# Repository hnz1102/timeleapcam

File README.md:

<div align="center">
  <h1><code>Time Leap Cam</code></h1>
  
</div>

# Time Leap Cam - Super Long Term Time-Lapse Camera and Monitoring by OpenAI

## Overview
The TIME LEAP CAM is an autofocus camera designed for long-duration time-lapse photography. Named for its ability to "leap" through time, this camera is ideal for monitoring over extended periods. It operates on battery power and features a DeepSleep mode to conserve energy when not actively shooting. Images are stored on a 64GB eMMC within one of eleven designated folders.

## What's New!
- 2024-08-12, If you want use on the XIAO ESP32S3 Sense module, please refer to the [XIAO_ESP32S3_SENSE branch](https://github.com/hnz1102/timeleapcam/tree/XIAO_ESP32S3_SENSE).

Update v0.3.3
- Improved the eMMC writing speed. The eMMC writing speed is improved by background writing. In the HD resolution, the writing speed is improved 28fps to 30fps. In the Full HD resolution, the writing speed is improved 6fps to 8fps. 
- JPEG quality can be set from 4 to 40. The default is 12. This value is high quality to set the value to 4. In the HD resolution, JPEG quality is set to less than 12, the writing speed is slower than 30fps. If you want to capture the image at 30fps, set the JPEG quality to 12 or more.
- If you want to direct write the image to the eMMC, set the 'Direct Write Mode' to checked. The image is directly written to the eMMC without the frame buffer. The writing speed is decreased. The default is unchecked.
- Changed the Allocate Unit Size to 32KB for the eMMC writing speed at the v0.3.3.

Update v0.3.2
- Add the 'System Temperature' to the status report. The temperature is measured by the internal temperature sensor of ESP32S3.
- Fixed the bug that when one-shot capture, the preview image is not displayed on the web.

Update v0.3.1
- Added the movie shooting function. The movie is created by combining the images taken at the specified cycle. 
 Capture Frames At Once (sec): The number of frames to capture at once. The default is 0, which means that the image is captured one by one. If you set it to 1, the image is captured during the 1 sec. If you set image resolution to VGA, the image is captured by 27 fps. HD is 15 - 27 fps. Full HD is 6 fps.
- Capture images are stored by appending the file. If you set to "Over Write Save", the image is overwritten. 
- Added the Open AI model 'GPT-4o mini' selection. The default is 'GPT-4o'. You can select the model from GPT-4o, GPT-4 Turbo, GPT-4o mini.
- If touch the button during 3 secs on the back, the camera starts the movie shooting. The movie shooting is stopped when the button is touched again.
- Improved the writing speed of the eMMC.
- Change the Report Interval: The default is 3600 sec. The report interval is changed to 3600 sec. The status report is sent to LINE when the specified cycle is reached.
- Camera interface is changed. Power Down, Reset pin is removed. In previous version, the power down pin and reset
pin are assigned by dumy GPIO pin. The 'esp-camera-rs' driver must be updated to the latest version.
- Fixed the bug that captured images are broken when the camera is in the DeepSleep mode. v0.3.1 is the stable version.
- Capturing clock is changed to 5MHz or 25MHz. The default is 5MHz when one image captured. When the movie is captured, the clock is changed to 25MHz.
- Changed the number of the frame buffer is 2. v0.3.0 set the number of the frame buffer to 3. But the eMMC writing speed is not enough to write the image to the eMMC. Since the eMMC writing speed is improved, the number of the frame buffer is changed to 2.
- Changed allocate_unit_size to 4096 for the eMMC writing speed at the v0.3.1.
- Fixed the bug that captured images are deleted when the camera is in the DeepSleep mode. v0.3.1 is fixed the bug.

Update v0.2.0
- Updated the UI for the configuration screen.
- Added the function to send a notification as status to LINE when the specified cycle is reached.
- Added the function to check the preview image on the web.
- Added images are uploaded to Cloudflare Images for private storage with signed URL.
- Added images are automatically deleted from the Cloudflare Images after 1 days.
- Added images can be downloaded as a compressed image from this camera on the web. (PC browser only)
- Added the function to check the remaining battery level on the web.
- Added the function to check the WiFi signal level on the web.
- Added the function to limit the time-lapse shooting time.
- Added the function to shoot when the camera touches the button during 3 secs on the back.

New Container Design
- The new container design is added for the camera

## Features
- **Autofocus Capability**: Ensures clear images over long shooting intervals.
- **Energy Efficiency**: Utilizes DeepSleep mode for minimal power consumption (less than 440uA, 1.5mW).
- **Wireless Charging**: Supports Qi wireless charging and automatically stops charging when full.
- **Water Resistance**: Suitable for outdoor use with splash resistance.
- **Advanced Notifications**: Uses OpenAI's GPT-4o/GPT-4o mini for image recognition and sends notifications via LINE when specific conditions are met.
- **Natural Language Configuration**: Set notification conditions in multiple languages through a simple interface.
- **Touch-Activated Web Server**: Access settings via a browser with automatic return to sleep mode after 5 minutes of inactivity.
- **Time Synchronization**: Uses NTP for automatic time adjustment when connected to WiFi, with RTC to maintain time offline.

## Specification
- **Resolution**: Up to 2592x1944 (QSXGA)
- **Sensor**: OV5640 5M pixel sensor
- **SoC Module**: ESP32-S3-WROOM-1-N16R8 (160MHz, 512KB SRAM, 16MB Flash, 8MB PSRAM)
- **Battery**: 3.7V LiPo 1100mAh
- **Storage**: 64GB eMMC
- **Connectivity**: WiFi 2.4GHz
- **Charging**: Qi wireless charging compatible
- **Dimensions**: 78(W) x 79(H) x 68(D) mm Box

## Usage
To use the TIME LEAP CAM, place it on a Qi wireless charger to charge power. Configure the camera settings such as shooting interval, time, and resolution through a web browser connected via WiFi. The camera can be activated from sleep mode by touching the screw on the back, which launches the web server for configuration.

## Options
- **Folder Selection**: Choose from 11 different folders for storing images.
- **Image Resolution**: Selectable up to QSXGA (2592x1944).
- **Notification Conditions**: Set via natural language input on the configuration screen.

## Notes
- **Water Immersion**: The camera is not designed to withstand full submersion in water.
- **API Keys Required**: To use the image recognition and notification features, obtain API keys from OpenAI, CloudFlare Images, and LINE Messaging API.
- **Internet Connection**: Required for using advanced features like image recognition and notifications. Time-lapse functionality is available without WiFi.

For API keys and more information, visit:
- OpenAI API: [https://openai.com/index/openai-api/](https://openai.com/index/openai-api/)
- CloudFlare Images: [https://developers.cloudflare.com/images/about](https://developers.cloudflare.com/images/about)
- LINE Messaging API: [https://developers.line.biz/en/docs/messaging-api/](https://developers.line.biz/en/docs/messaging-api/)
# How to build from code and Install to the unit.

Using Ubuntu 22.04.3 LTS and ESP-IDF V5.2.1

## Prerequisites
Before proceeding with the installation, ensure that your system meets the following requirements:
- Operating System: Linux-based distribution
- Required Packages: git, python3, python3-pip, gcc, build-essential, curl, pkg-config, libudev-dev, libtinfo5, clang, libclang-dev, llvm-dev, udev, libssl-dev, python3.10-venv

## Installation Steps

### 1. System Update and Package Installation
Update your system and install the necessary packages using:
```bash
sudo apt update && sudo apt -y install git python3 python3-pip gcc build-essential curl pkg-config libudev-dev libtinfo5 clang libclang-dev llvm-dev udev libssl-dev python3.10-venv
```

### 2. Rust Installation
Install Rust programming language and Cargo package manager:
```bash
curl --proto '=https' --tlsv1.2 -sSf https://sh.rustup.rs | sh
```
After installation, activate Rust by sourcing the environment:
```bash
. "$HOME/.cargo/env"
```

### 3. Additional Tools Installation
Install the following Rust tools:
- ldproxy
- espup
- cargo-espflash

Use the following commands:
```bash
cargo install ldproxy
cargo install espup
cargo install cargo-espflash
```
2024-08-12, cargo-espflash can not be compiled.
If you have an error, use the following command.
```bash
cargo install cargo-binstall
cargo binstall cargo-espflash 
```

### 4. ESP Environment Setup
Run the following command to install and update the Espressif Rust ecosystem:
```bash
espup install
espup update
```
Set up environment variables:
```bash
. ./export-esp.sh
```

### 5. Udev Rules Configuration
Configure udev rules for device permissions:
```bash
sudo sh -c 'echo "SUBSYSTEMS==\"usb\", ATTRS{idVendor}==\"303a\", ATTRS{idProduct}==\"1001\", MODE=\"0666\"" > /etc/udev/rules.d/99-esp32.rules'
sudo udevadm control --reload-rules
sudo udevadm trigger
```

### 6. Clone Repository
Clone the TimeLeapCam repository:
```bash
git clone https://github.com/hnz1102/timeleapcam.git
cd timeleapcam/code/
```

### 7. Setting WiFi SSID, Password, etc.
Change the following the configuration file.
```bash
cfg.toml

[timeleapcam]
wifi_ssid = "<Your AP SSID>"  # Set your AP SSID
wifi_psk = "<Your AP Password>" # Set your AP Password
http_server = "" # NOT USED
resolution = "8"
track_id = "0"
timezone_offset = "9"
auto_capture = "false"
idle_in_sleep_time = "300"
duration = "0"
api_key = "<API KEY for openAI>" # Set your OpenAI API Key
model = "gpt-4o"
query_openai = "false"
query_prompt = "If heavy rain is expected in 30 minutes, please include a 'NOTICE' with the reason in your reply. If not, simply respond with 'NONE'. Heavy rain is defined as 30mm/h or more."
post_account = "<Your LINE Account ID>" # Set your LINE Account ID
post_access_token = "<Access Token for LINE Message>" # Set your LINE Access Token
storage_account = "<Your Cloudflare Account ID>" # Set your Cloudflare Account ID
storage_access_token = "<Your Cloudflare Access Token>" # Set your Cloudflare Access Token
storage_signed_key = "<Your Cloudflare Image Signed Key>" # Set your Cloudflare Image Signed Key
post_message_trigger = "NOTICE"
autofocus_once = "true"
status_report = "false"
status_report_interval = "3600"
post_interval = "3600"
leap_day = "-1"
leap_hour = "-1"
leap_minute = "-1"
capture_frames_at_once = "0"
overwrite_saved = "false"
```

### 8. Build and Flash
Build the project and flash it to your device:
```bash
cargo build --release
cargo espflash flash --release --monitor
```
At the first boot, the device will format the eMMC and create the necessary folders. This process may take a few minutes.

## Schematic, PCB Gabar and Container 3D Data

There is a Schematic data in the hardware directory including 3D printing data. 

### New Cover and Base for the Camera

Base for the camera is also available for 3D printing. base-v14.stl is the latest version.

## Troubleshooting
- **Permission Issues**: Ensure udev rules are set correctly and you have the necessary permissions to access the device.
- **Build Errors**: Check that all dependencies are installed correctly. If errors persist, try cleaning the project with `cargo clean` and rebuild.

## LICENSE
This source code is licensed under MIT. Other Hardware Schematic documents are licensed under CC-BY-SA V4.0.

This project uses the following libraries and resources:
  
https://github.com/jlocash/esp-camera-rs

https://github.com/0015/ESP32-OV5640-AF

These libraries are licensed under each library's respective licenses.

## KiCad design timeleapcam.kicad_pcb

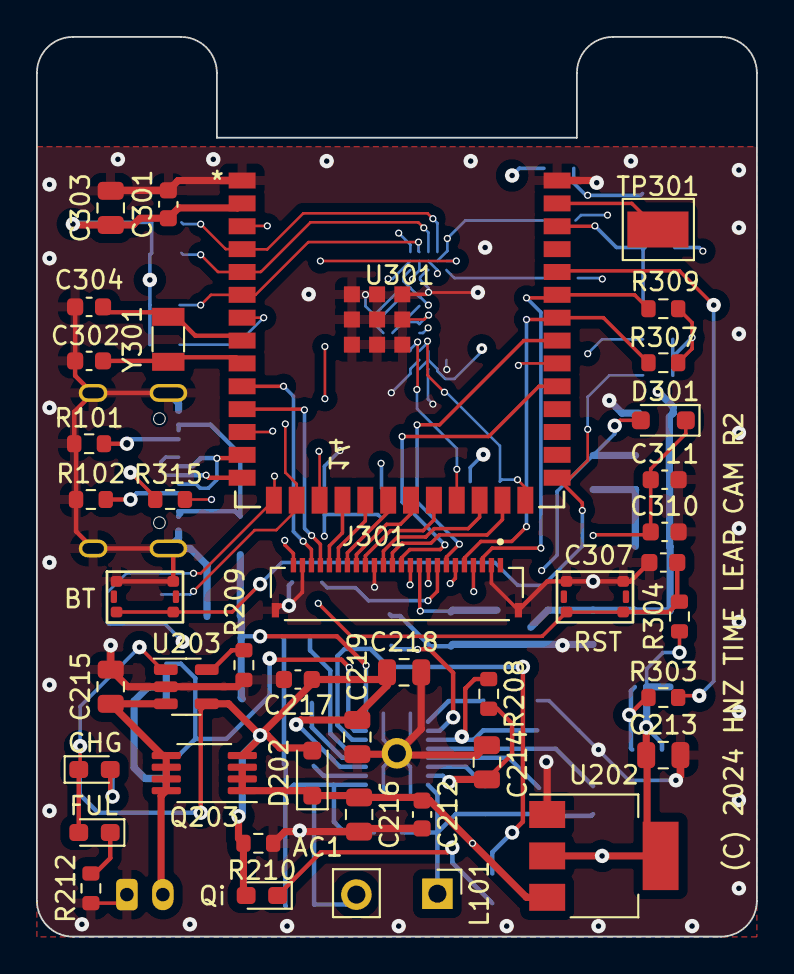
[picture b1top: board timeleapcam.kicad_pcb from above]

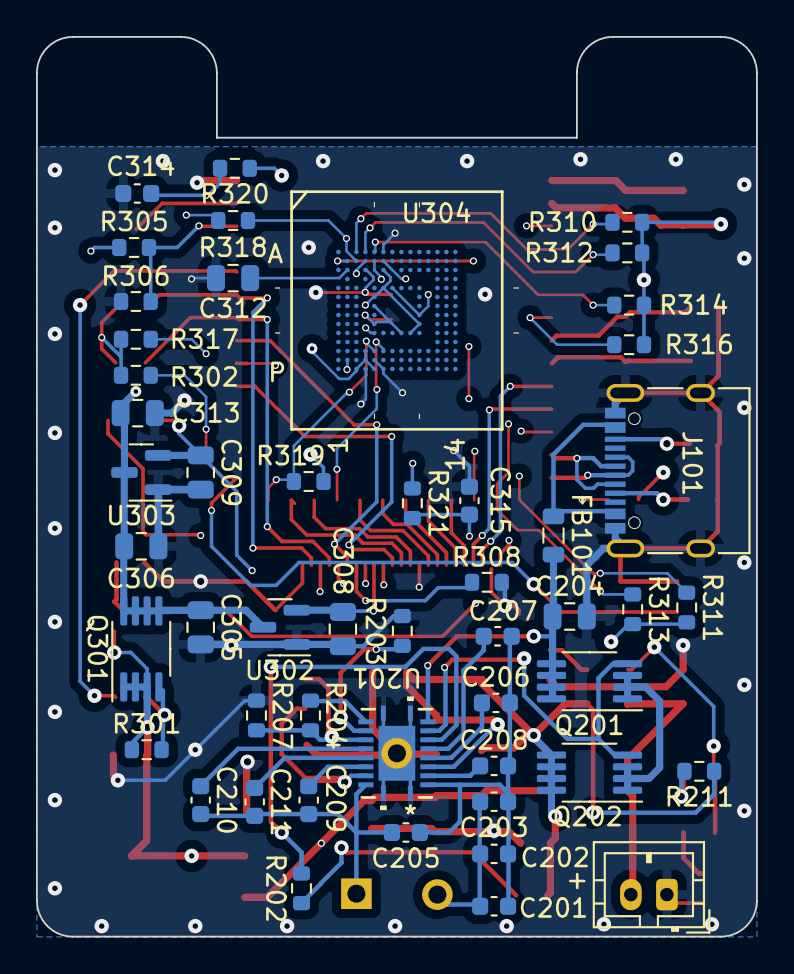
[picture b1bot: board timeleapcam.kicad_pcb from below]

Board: 4 copper layers, 40.0 x 50.0 mm, 91 parts (50 on the bottom side), 72 nets.

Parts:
C201, C207, C210: 22nF/25V; C_0603_1608Metric
C202, C208, C209: 0.01uF/25V; C_0603_1608Metric
C203, C217: 0.1uF/25V; C_0603_1608Metric
C204, C216, C218, C305, C306, C308, C309, C312, C313: 1uF; C_0805_2012Metric
C205: 2000pF/25V; C_0603_1608Metric
C206, C211: 0.47uF/25V; C_0603_1608Metric
C212, C301, C307, C310, C314, C315: 0.1uF; C_0603_1608Metric
C213, C303: 10uF; C_0805_2012Metric
C214, C219: 22uF; C_0805_2012Metric
C215: 4.7uF; C_0805_2012Metric
C302, C304: 16pF; C_0603_1608Metric
C311: 2.2uF; C_0603_1608Metric
D201, D203: LED RED; LED_0603_1608Metric_Pad1.05x0.95mm_HandSolder
D202, D301: NSR0340HT1G; D_SOD-323_HandSoldering
D204: LED GREEN; LED_0603_1608Metric_Pad1.05x0.95mm_HandSolder
FB101: MH2029-601Y; L_0805_2012Metric
J101: USB4105-GF-A; USB_C_5077CR-16-SMC2-BK-TR
J201: LiPo BATTERY; JST_PH_B2B-PH-K_1x02_P2.00mm_Vertical
J301: FH34SRJ-24S-0.5SH50; HRS_FH34SRJ-24S-0.5SH_50_
L101: WR483265-15F5-G; PinHole_1x02_P4.5mm_Vertical
Q201, Q202, Q203, Q301: IRF7606TRPBF; MSOP-8_3x3mm_P0.65mm
R101, R102: 5.1K; R_0603_1608Metric
R202, R303: 1K; R_0603_1608Metric
R203, R208, R301, R302, R304, R308, R310, R311, R312, R313, R314, R315, R316, R317, R318, R319, R320, R321: 10K; R_0603_1608Metric
R204: 110 1%; R_0603_1608Metric
R207: 150 1%; R_0603_1608Metric
R209: 2K; R_0603_1608Metric
R210: 100K; R_0603_1608Metric
R211, R212: 330; R_0603_1608Metric
R305, R306: 51K 1%; R_0603_1608Metric
R307, R309: 4.7K; R_0603_1608Metric
SW301, SW302: 3.5x2.6 Tact SW; WS-TASV SMT Tact Switch
TP301: TOUCHSW; TestPoint_Pad_3.2x1.6mm
U201: BQ51013BRHLR; RHL20_2P05X3P05
U202: LD1117S33TR_SOT223; SOT-223-3_TabPin2
U203: MCP73831-2-OT; SOT-23-5
U301: ESP32-S3-WROOM-1-N16R8; ESP32-S3-WROOM-1_EXP
U302: MCP1700T-1802E/TT; SOT-23
U303: MCP1700T-2802E/TT; SOT-23
U304: FEMC064G-M11; EM32VSUKN FPGA153
Y301: 32.7680KHz; Crystal_SMD_3215-2Pin_3.2x1.5mm

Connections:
+1V8: C308.1, J301.10, U302.2 (VO)
+2V8: C309.1, D301.2 (A), J301.4, J301.11, U303.2 (VO)
+3.3V: C213.1, C301.1, C303.1, Q301.1 (S), Q301.2 (S), Q301.3 (S), R301.1, R302.1, R304.1, R307.1, R309.1, R310.1, R311.2, R312.1, R313.2, R314.1, R315.2, R316.1, R317.2, R318.1, R319.2, U202.2 (VO), U301.2 (3V3)
/USBDM: J101.A7 (D-), J101.B7 (D-), U301.13 (IO19)
/USBDP: J101.A6 (D+), J101.B6 (D+), U301.14 (IO20)
/USBVDD: C204.1, FB101.2, Q201.5 (D), Q201.6 (D), Q201.7 (D), Q201.8 (D), U201.9 (AD)
/esp32-cam-emmc/AFVDD2V8: C310.1, C311.1, D301.1 (K), J301.24
/esp32-cam-emmc/IO0/BOOT: R302.2, SW301.3 (K), SW301.4 (A), U301.27 (IO0)
/esp32-cam-emmc/IO1/TOUCHSW1: TP301.1, U301.39 (IO1)
/esp32-cam-emmc/IO2/BATVOL: R305.2, R306.1, U301.38 (IO2)
/esp32-cam-emmc/IO3/MMC_D5: R311.1, U301.15 (IO3), U304.B4 (DAT5)
/esp32-cam-emmc/IO4/MMC_D0: R310.2, U301.4 (IO4), U304.A3 (DAT0)
/esp32-cam-emmc/IO5/MMC_D1: R312.2, U301.5 (IO5), U304.A4 (DAT1)
/esp32-cam-emmc/IO6/MMC_D2: R314.2, U301.6 (IO6), U304.A5 (DAT2)
/esp32-cam-emmc/IO7/MMC_D3: R316.2, U301.7 (IO7), U304.B2 (DAT3)
/esp32-cam-emmc/IO8/MMC_D4: R318.2, U301.12 (IO8), U304.B3 (DAT4)
/esp32-cam-emmc/IO9/MMC_D7: R315.1, U301.17 (IO9), U304.B6 (DAT7)
/esp32-cam-emmc/IO10/Y5: J301.20, U301.18 (IO10)
/esp32-cam-emmc/IO11/Y2: J301.19, U301.19 (IO11)
/esp32-cam-emmc/IO12/Y6: J301.18, U301.20 (IO12)
/esp32-cam-emmc/IO13/PCLK: J301.17, U301.21 (IO13)
/esp32-cam-emmc/IO14/Y7: J301.16, U301.22 (IO14)
/esp32-cam-emmc/IO15/XTAL32KP: C304.1, U301.8 (IO15), Y301.2
/esp32-cam-emmc/IO16/XTAL32KN: C302.1, U301.9 (IO16), Y301.1
/esp32-cam-emmc/IO17/Y4: J301.22, U301.10 (IO17)
/esp32-cam-emmc/IO18/Y3: J301.21, U301.11 (IO18)
/esp32-cam-emmc/IO21/MMC_CLK: R317.1, U301.23 (IO21), U304.M6 (CLK)
/esp32-cam-emmc/IO38/Y9: J301.12, U301.31 (IO38)
/esp32-cam-emmc/IO39/HREF: J301.9, U301.32 (IO39)
/esp32-cam-emmc/IO40/VSYNC: J301.7, U301.33 (IO40)
/esp32-cam-emmc/IO41/SCL: J301.5, R307.2, U301.34 (IO41)
/esp32-cam-emmc/IO42/SDA: J301.3, R309.2, U301.35 (IO42)
/esp32-cam-emmc/IO45/MMC_CMD: R319.1, U301.26 (IO45), U304.M5 (CMD)
/esp32-cam-emmc/IO46/MMC_D6: R313.1, U301.16 (IO46), U304.B5 (DAT6)
/esp32-cam-emmc/IO47/Y8: J301.14, U301.24 (IO47)
/esp32-cam-emmc/IO48/XMCLK: J301.13, U301.25 (IO48)
/esp32-cam-emmc/PWDN: J301.8, R308.1
/esp32-cam-emmc/RXD0/IO44/~CAMVDD: R303.2, U301.36 (RXD0)
/esp32-cam-emmc/eMMC_PWR: C305.1, C306.1, C313.1, Q301.5 (D), Q301.6 (D), Q301.7 (D), Q301.8 (D), R320.1, R321.1, U302.3 (VI), U303.3 (VI), U304.C6 (VCCQ), U304.E6 (VCC), U304.F5 (VCC), U304.J10 (VCC), U304.K9 (VCC), U304.M4 (VCCQ), U304.N4 (VCCQ), U304.P3 (VCCQ), U304.P5 (VCCQ)
/esp32-cam-emmc/~CAM_RESET: C315.1, J301.6, R321.2
/esp32-cam-emmc/~RESET: C307.1, R304.2, SW302.3 (K), SW302.4 (A), U301.3 (EN)
/qi-reveiver/AC1: C201.2, C202.2, C203.2, L101.2
/qi-reveiver/AC2: C205.2, C209.2, C210.2, C211.2, L101.1, U201.19 (AC2)
/qi-reveiver/QIVDD: C217.1, C218.1, C219.1, D201.2 (A), D202.2 (A), Q202.5 (D), Q202.6 (D), Q202.7 (D), Q202.8 (D), Q203.4 (G), R210.1, R211.1, U201.4 (OUT), U203.4 (V_{DD})
/qi-reveiver/VBAT: C215.1, J201.2, Q203.5 (D), Q203.6 (D), Q203.7 (D), Q203.8 (D), U203.3 (V_{BAT})
/qi-reveiver/VOUT: C212.1, C216.1, D202.1 (K), Q203.1 (S), Q203.2 (S), Q203.3 (S), R305.1, U202.3 (VI)
GND: C204.2, C212.2, C213.2, C214.2, C215.2, C216.2, C217.2, C218.2, C219.2, C301.2, C302.2, C303.2, C304.2, C305.2, C306.2, C307.2, C308.2, C309.2, C310.2, C311.2, C312.2, C313.2, C314.2, C315.2, J101.A1 (GND), J101.A12 (GND), J101.B1 (GND), J101.B12 (GND), J101.S1 (SHIELD), J201.1, J301.2, J301.15, J301.23, J301.25, J301.26, R101.1, R102.1, R203.1, R207.1, R209.2, R210.2, R212.2, R306.2, R308.2, SW301.1, SW301.2, SW302.1, SW302.2, U201.1 (PGND), U201.10 (EN1), U201.11 (EN2), U201.20 (PGND), U201.21 (EPAD), U202.1 (GND), U203.2 (V_{SS}), U301.1 (GND), U301.40 (GND), U301.41 (GND), U301.42 (GND), U301.43 (GND), U301.44 (GND), U301.45 (GND), U301.46 (GND), U301.47 (GND), U301.48 (GND), U301.49 (GND), U302.1 (GND), U303.1 (GND), U304.A6 (VSS), U304.C4 (VSSQ), U304.E7 (VSS), U304.G5 (VSS), U304.H10 (VSS), U304.J5 (VSS), U304.K8 (VSS), U304.N2 (VSSQ), U304.N5 (VSSQ), U304.P4 (VSSQ), U304.P6 (VSSQ)
unnamed: D201.1 (K), R202.1
unnamed: D203.2 (A), R211.2
unnamed: D203.1 (K), D204.2 (A), U203.1 (STAT)
unnamed: D204.1 (K), R212.1
unnamed: FB101.1, J101.A4 (VBUS), J101.A9 (VBUS), J101.B4 (VBUS), J101.B9 (VBUS)
unnamed: J101.A5 (CC1), R102.2
unnamed: J101.B5 (CC2), R101.2
unnamed: Q201.4 (G), Q202.4 (G), U201.8 (~AD-EN)
unnamed: Q201.1 (S), Q201.2 (S), Q201.3 (S), Q202.1 (S), Q202.2 (S), Q202.3 (S)
unnamed: Q301.4 (G), R301.2, R303.1
unnamed: C201.1, C202.1, C203.1, C205.1, C206.2, C207.2, C208.2, U201.2 (AC1)
unnamed: C208.1, U201.3 (BOOT1)
unnamed: C209.1, U201.17 (BOOT2)
unnamed: C206.1, U201.5 (CLMP1)
unnamed: C211.1, U201.16 (CLMP2)
unnamed: C207.1, U201.6 (COM1)
unnamed: C210.1, U201.15 (COM2)
unnamed: R204.1, R207.2, R208.1, U201.14 (FOD)
unnamed: R204.2, U201.12 (ILIM)
unnamed: C214.1, R208.2, U201.18 (RECT)
unnamed: R203.2, U201.13 (TS-CTRL)
unnamed: R202.2, U201.7 (~CHG)
unnamed: R209.1, U203.5 (PROG)
unnamed: C312.1, U304.C2 (VDDI)
unnamed: C314.1, R320.2, U304.K5 (~RST)

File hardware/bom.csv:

Designator,Footprint,Quantity,Value,LCSC Part #
"C201, C207, C210",0603,3,22nF/25V,
"C202, C208, C209",0603,3,0.01uF/25V,
"C203, C217",0603,2,0.1uF/25V,
"C204, C216, C218, C305, C306, C308, C309, C312, C313",0805,9,1uF,
C205,0603,1,2000pF/25V,
"C206, C211",0603,2,0.47uF/25V,
"C212, C301, C307, C310, C314, C315",0603,6,0.1uF,
"C213, C303",0805,2,10uF,
"C214, C219",0805,2,22uF,
C215,0805,1,4.7uF,
"C302, C304",0603,2,16pF,
C311,0603,1,2.2uF,
"D201, D203",0603,2,LED RED,
"D202, D301",D_SOD-323_HandSoldering,2,NSR0340HT1G,
D204,0603,1,LED GREEN,
FB101,0805,1,MH2029-601Y,
J101,USB_C_5077CR-16-SMC2-BK-TR,1,USB4105-GF-A,
J201,JST_PH_B2B-PH-K_1x02_P2.00mm_Vertical,1,LiPo BATTERY,
J301,HRS_FH34SRJ-24S-0.5SH_50_,1,FH34SRJ-24S-0.5SH50,
L101,PinHole_1x02_P4.5mm_Vertical,1,WR483265-15F5-G,
"Q201, Q202, Q203, Q301",MSOP-8_3x3mm_P0.65mm,4,IRF7606TRPBF,
"R101, R102",0603,2,5.1K,
"R202, R303",0603,2,1K,
"R203, R208, R301, R302, R304, R308, R310, R311, R312, R313, R314, R315, R316, R317, R318, R319, R320, R321",0603,18,10K,
R204,0603,1,110 1%,
R207,0603,1,150 1%,
R209,0603,1,2K,
R210,0603,1,100K,
"R211, R212",0603,2,330,
"R305, R306",0603,2,51K 1%,
"R307, R309",0603,2,4.7K,
"SW301, SW302",WS-TASV SMT Tact Switch,2,3.5x2.6 Tact SW,
TP301,TestPoint_Pad_3.2x1.6mm,1,TOUCHSW,
U201,RHL20_2P05X3P05,1,BQ51013BRHLR,
U202,SOT-223-3_TabPin2,1,LD1117S33TR_SOT223,
U203,SOT-23-5,1,MCP73831-2-OT,
U301,ESP32-S3-WROOM-1_EXP,1,ESP32-S3-WROOM-1-N16R8,
U302,SOT-23,1,MCP1700T-1802E/TT,
U303,SOT-23,1,MCP1700T-2802E/TT,
U304,EM32VSUKN FPGA153,1,"FEMC064G-M11
",
Y301,Crystal_SMD_3215-2Pin_3.2x1.5mm,1,32.7680KHz,

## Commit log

2024-05-25 Rev2
2024-05-26 Change Regulator IC and Pullup R
2024-05-30 remove .gitmoudles
2024-05-30 add esp-camera-rs driver as submodule
2024-05-30 Add .cargo/config.toml
2024-05-30 fixed .cargo/config.toml
2024-05-30 remove comment lines
2024-05-31 Add espflash.toml for new cargo-espflash
2024-06-02 Add to show wifi status
2024-06-04 Fixed crash on boot
2024-06-04 Change camera pin assign for evt2 board
2024-06-04 Add README.md etc.
2024-06-04 Fixed README
2024-06-06 Fixed panic when capture image
2024-06-06 for XIAO_ESP32S3_SENSE board
2024-06-06 Change reglator more low power
2024-06-08 Add print ssid, ip address info.
2024-06-08 Change container
2024-06-11 Fixed sdcard access
2024-06-15 Improving UI
2024-06-15 Add status report
2024-06-16 Add a feature downloding images
2024-06-20 Add during capture time
2024-06-22 Add signed_url for security
2024-06-22 v0.2.0 version code and contaier
2024-06-22 Update git2 CVE-2023-22742
2024-06-22 Fixed hunging when images are deleted
2024-08-09 v0.3.0
2024-08-10 v0.3.1
2024-08-12 Add work arround cargo-espflash install error
2024-08-14 for XIAO ESP32S3 Sense
2024-08-14 Add link
2024-08-14 Add reference to XIAO_ESp32S3_SENSE
2024-08-15 Fixed git command line branch
2024-08-15 Fixed SD mount error
2024-08-17 Change to use SDSPI for SDCardHost
2024-08-17 v0.3.2
2024-08-22 v0.3.3
2024-08-25 fixed count captured frames
2024-08-29 Set WiFi Tx power to 60.
2024-08-29 Touch pad sensor is more sensitive
2024-08-29 Wait 3sec before capture from deep sleep
2024-08-29 Fixed panic when wakeup from deep sleep
2024-09-01 Fixed the bug direct write mode does not work.
2024-09-01 Fixed the bug Drirect Write Mode switch can not changed on Capture menu.
2024-09-01 Add indicator for capturing use GPIO2 LED
2024-09-02 Wait capture to prevent image corrupt
2024-09-02 Easy capture image
2024-09-02 Use Dynamic TLS Buffer
2024-09-02 Change IDF Version to 5.2.2
2024-09-02 show free internal heap size for debug
2024-09-02 Change default openai model to gpt-4o-mini.
2024-09-04 Fixed to get slow a image when there are a lot of images in storage.
2024-09-04 Use TLS dynamic buffer, avoid to short of memory
2024-09-04 Change IDF version to v5.2.2
2024-09-06 reconnect wifi when it is disconnected

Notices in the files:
timeleapcam.kicad_pcb:
(C) 2024 HNZ TIME LEAP CAM R2
